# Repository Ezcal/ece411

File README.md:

# ece411
Practicum Project for ECE411 - Fall 2015
### Team Name: Sagutinhoun
### Group members:
Miguel Garcia de los Santos, Sabin Maharjan, Christina Nelson, and Calhoun Zabel

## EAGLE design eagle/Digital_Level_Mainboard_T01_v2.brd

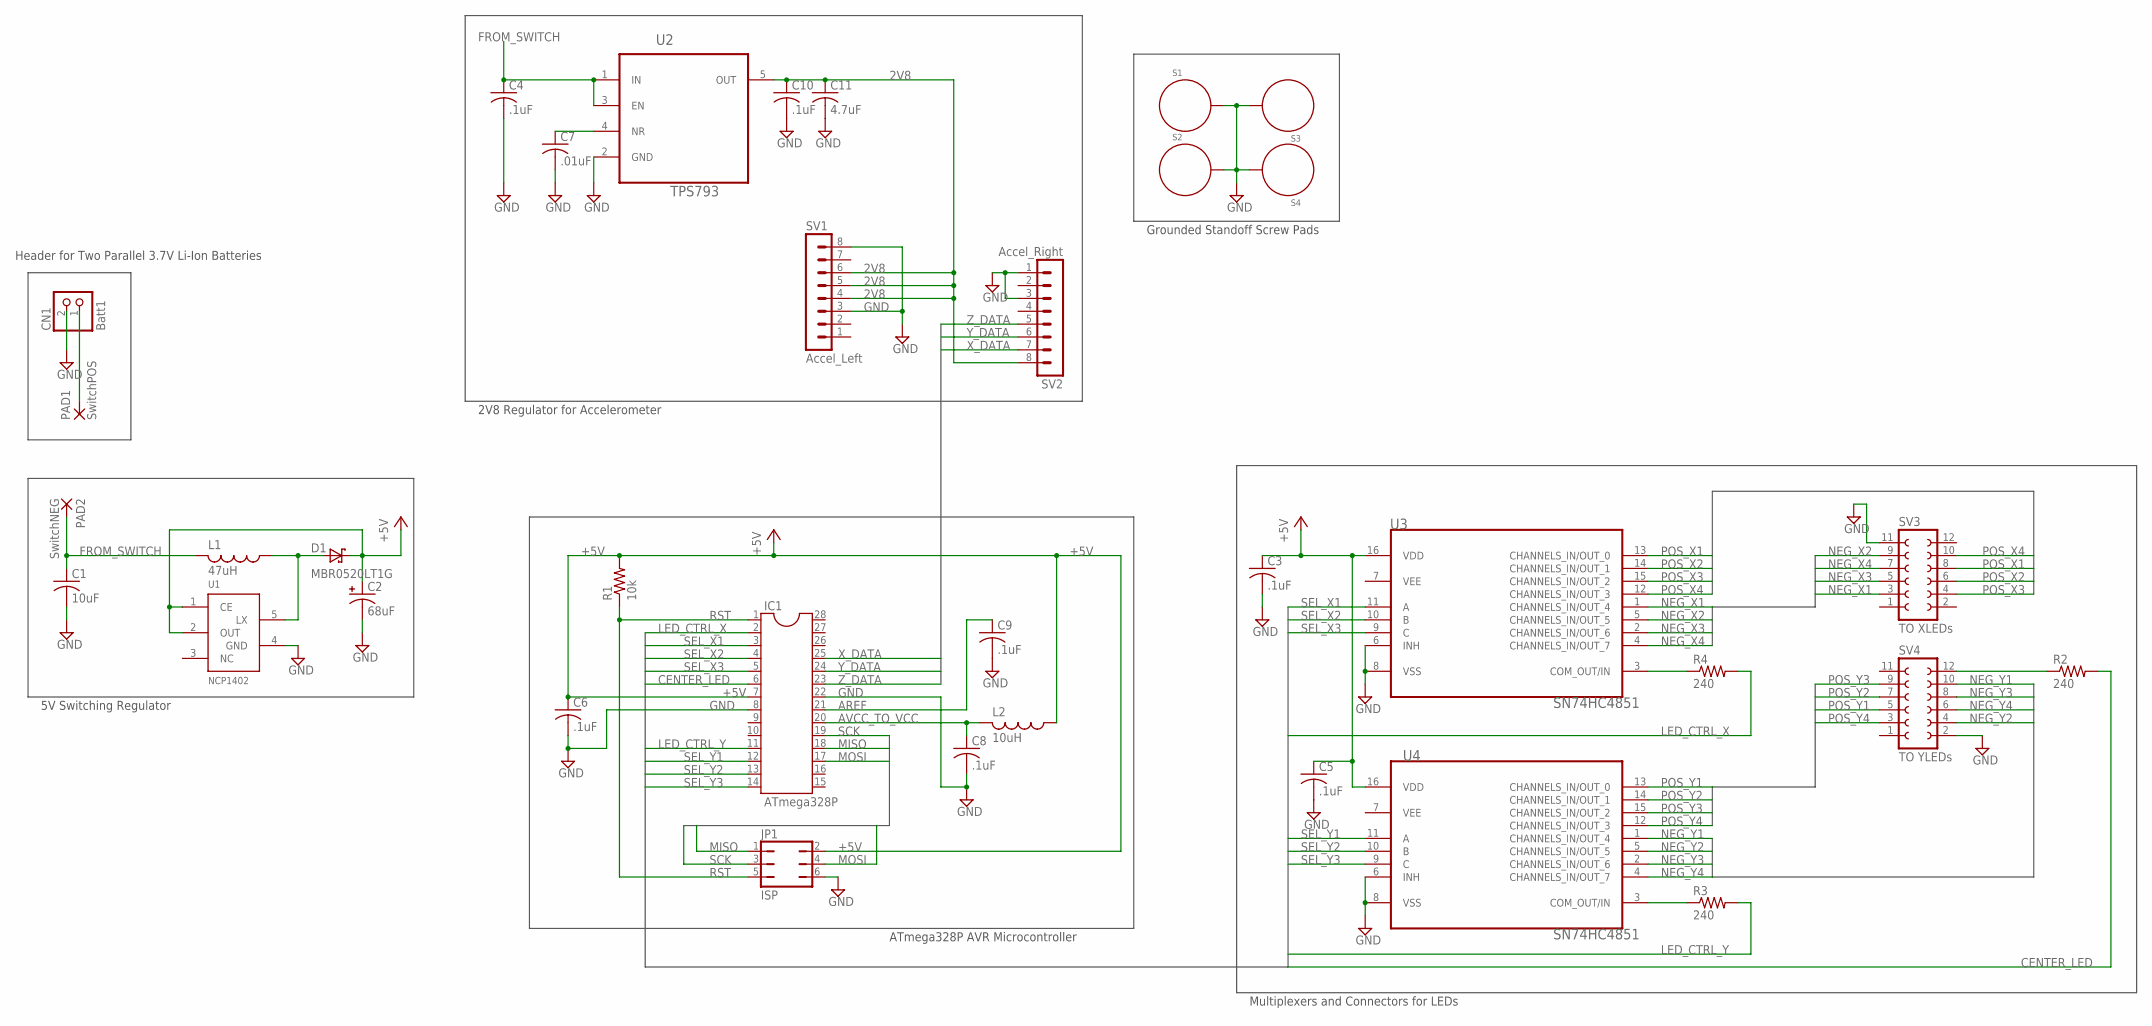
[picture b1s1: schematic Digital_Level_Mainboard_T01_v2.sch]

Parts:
C1: 10uF; C1206K
C2: 68uF; 2312_CAP
C3, C4, C5, C6, C8, C9, C10: .1uF; C1206K
C7: .01uF; C1206K
C11: 4.7uF; C1206K
CN1: Batt1; JST-PH-2-SMT
D1: MBR0520LT1G; MBR0520
IC1: ATmega328P; DIL28-3
JP1: ISP; JP3Q
L1: 47uH; BOURNS_INDUCTOR
L2: 10uH; L1812
PAD1: SwitchPOS; 2,54/1,1
PAD2: SwitchNEG; 2,54/1,1
R1: 10k; R0805
R2, R3, R4: 240; R1206
S1, S2, S3, S4: STANDOFF_ELECTRICAL; STANDOFF-ELECTRICAL
SV1: Accel_Left; MA08-1
SV2: Accel_Right; MA08-1
SV3: TO XLEDs; FE06-2
SV4: TO YLEDs; FE06-2
U1: NCP1402; WSON-8
U2: TPS793; SOT95P280X145-5N
U3, U4: SN74HC4851; DIP254P762X508-16

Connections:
2V8: C10.1, C11.1, SV1.4, SV1.5, SV1.6, SV2.8, U2.5 (OUT)
5V_REG1_LX: D1.P$2 (A), L1.P$1 (1), U1.5 (LX)
+5V: C2.P (1), C3.1, C5.1, C6.1, D1.P$1 (K), IC1.7, JP1.2, L2.1, R1.2, U1.1 (CE), U1.2 (OUT), U3.16 (VDD), U4.16 (VDD)
AREF: C9.1, IC1.21
AVCC_TO_VCC: C8.1, IC1.20, L2.2
CENTER_LED: IC1.6, R2.2
CENTER_LED_CONN: R2.1, SV4.12
CTRL_X_TO_MUX: R4.1, U3.3 (COM_OUT/IN)
CTRL_Y_TO_MUX: R3.1, U4.3 (COM_OUT/IN)
FROM_SWITCH: C1.1, C4.1, L1.P$2 (2), PAD2.1, U2.1 (IN), U2.3 (EN)
GND: C1.2, C2.N (2), C3.2, C4.2, C5.2, C6.2, C7.2, C8.2, C9.2, C10.2, C11.2, CN1.2 (1), IC1.8, IC1.22, JP1.6, S1.P1, S2.P1, S3.P1, S4.P1, SV1.3, SV1.8, SV2.1, SV2.3, SV3.11, SV4.2, U1.4 (GND), U2.2 (GND), U3.6 (INH), U3.8 (VSS), U4.6 (INH), U4.8 (VSS)
LED_CTRL_X: IC1.2, R4.2
LED_CTRL_Y: IC1.11, R3.2
LIN-REG_NR-PIN: C7.1, U2.4 (NR)
MISO: IC1.18, JP1.1
MOSI: IC1.17, JP1.4
NEG_X1: SV3.3, U3.1 (CHANNELS_IN/OUT_4)
NEG_X2: SV3.9, U3.5 (CHANNELS_IN/OUT_5)
NEG_X3: SV3.5, U3.2 (CHANNELS_IN/OUT_6)
NEG_X4: SV3.7, U3.4 (CHANNELS_IN/OUT_7)
NEG_Y1: SV4.10, U4.1 (CHANNELS_IN/OUT_4)
NEG_Y2: SV4.4, U4.5 (CHANNELS_IN/OUT_5)
NEG_Y3: SV4.8, U4.2 (CHANNELS_IN/OUT_6)
NEG_Y4: SV4.6, U4.4 (CHANNELS_IN/OUT_7)
POS_BATT: CN1.1 (2), PAD1.1
POS_X1: SV3.8, U3.13 (CHANNELS_IN/OUT_0)
POS_X2: SV3.6, U3.14 (CHANNELS_IN/OUT_1)
POS_X3: SV3.4, U3.15 (CHANNELS_IN/OUT_2)
POS_X4: SV3.10, U3.12 (CHANNELS_IN/OUT_3)
POS_Y1: SV4.5, U4.13 (CHANNELS_IN/OUT_0)
POS_Y2: SV4.7, U4.14 (CHANNELS_IN/OUT_1)
POS_Y3: SV4.9, U4.15 (CHANNELS_IN/OUT_2)
POS_Y4: SV4.3, U4.12 (CHANNELS_IN/OUT_3)
RST: IC1.1, JP1.5, R1.1
SCK: IC1.19, JP1.3
SEL_X1: IC1.3, U3.11 (A)
SEL_X2: IC1.4, U3.10 (B)
SEL_X3: IC1.5, U3.9 (C)
SEL_Y1: IC1.12, U4.11 (A)
SEL_Y2: IC1.13, U4.10 (B)
SEL_Y3: IC1.14, U4.9 (C)
X_DATA: IC1.25, SV2.7
Y_DATA: IC1.24, SV2.6
Z_DATA: IC1.23, SV2.5

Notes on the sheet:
Header for Two Parallel 3.7V Li-Ion Batteries
5V Switching Regulator
2V8 Regulator for Accelerometer
Grounded Standoff Screw Pads
Multiplexers and Connectors for LEDs
ATmega328P AVR Microcontroller

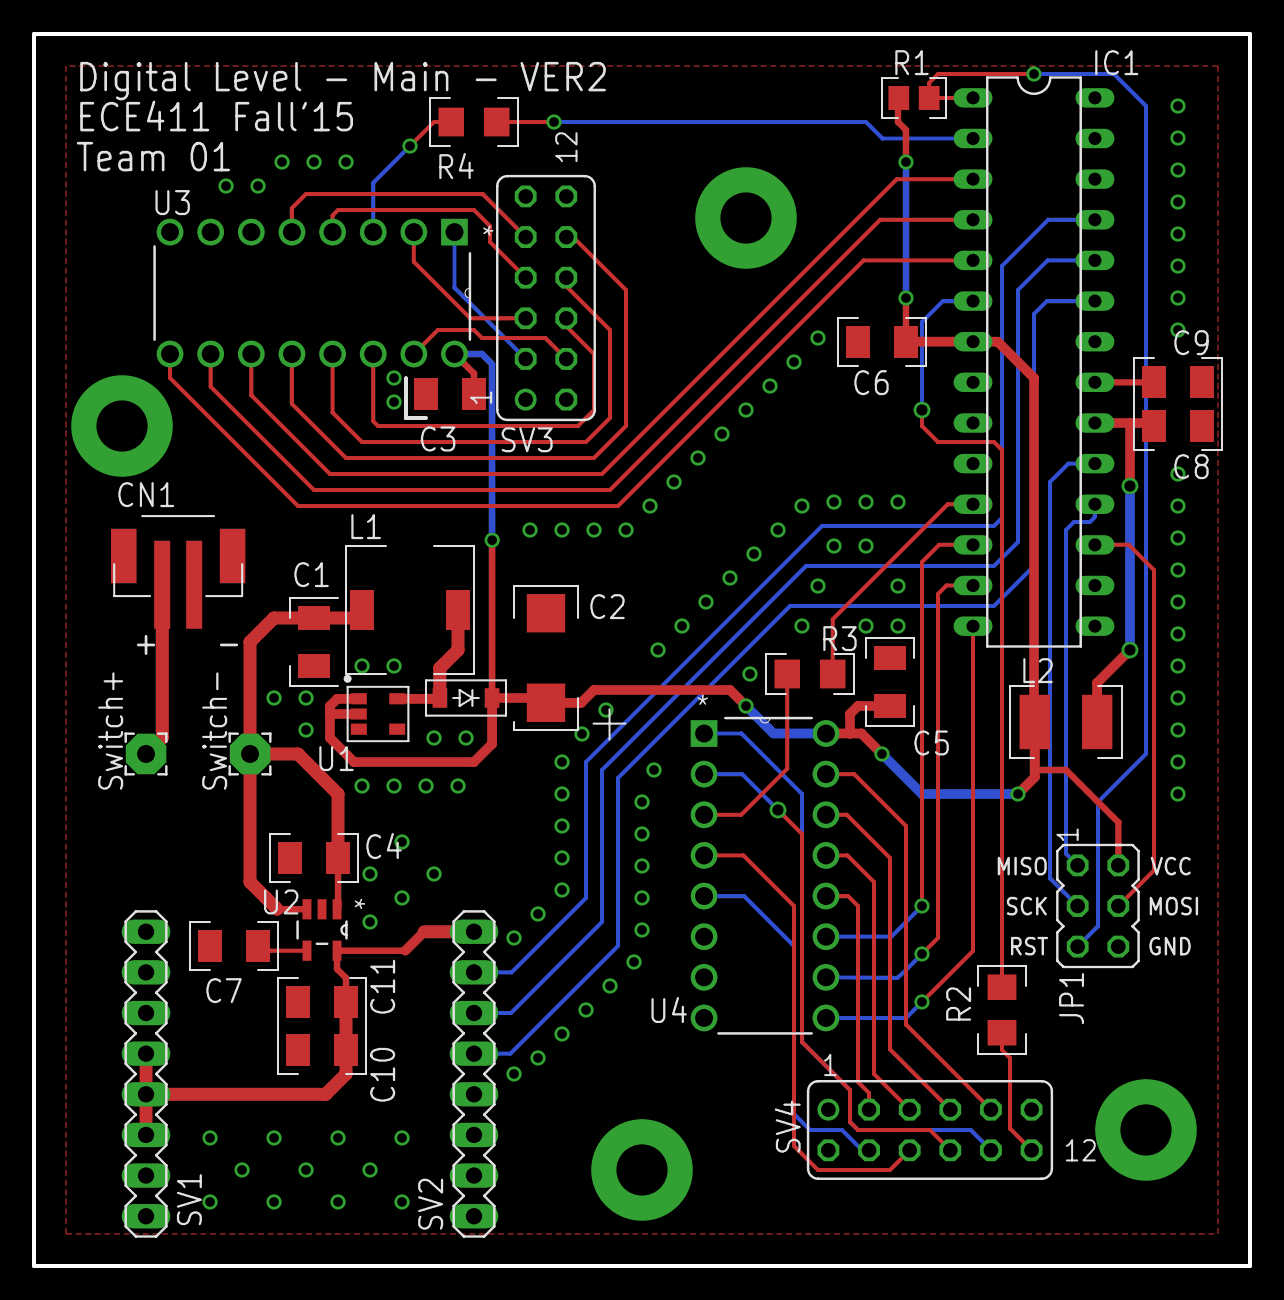
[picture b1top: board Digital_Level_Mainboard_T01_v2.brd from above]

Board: 2 copper layers, 76.0 x 77.0 mm, 35 parts (0 on the bottom side), 44 nets.

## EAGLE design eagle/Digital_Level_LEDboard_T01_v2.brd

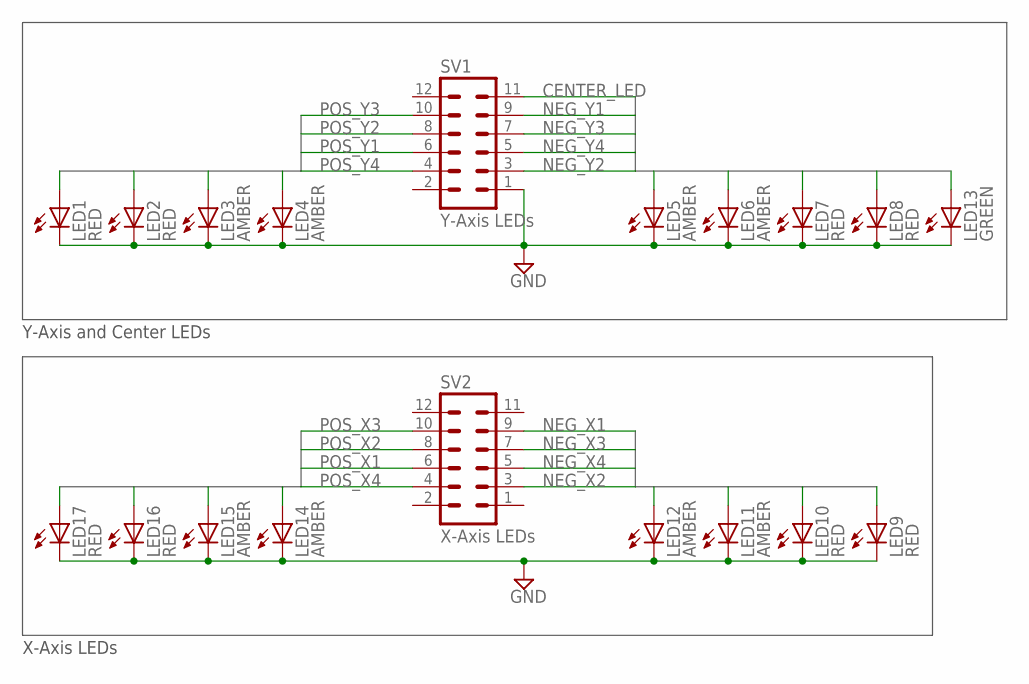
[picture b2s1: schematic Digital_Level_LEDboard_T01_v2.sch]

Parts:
LED1, LED2, LED7, LED8, LED9, LED10, LED16, LED17: RED; LED5MM
LED3, LED4, LED5, LED6, LED11, LED12, LED14, LED15: AMBER; LED5MM
LED13: GREEN; LED5MM
SV1: Y-Axis LEDs; MA06-2
SV2: X-Axis LEDs; MA06-2

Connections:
CENTER_LED: LED13.A, SV1.11
GND: LED1.K (C), LED2.K (C), LED3.K (C), LED4.K (C), LED5.K (C), LED6.K (C), LED7.K (C), LED8.K (C), LED9.K (C), LED10.K (C), LED11.K (C), LED12.K (C), LED13.K (C), LED14.K (C), LED15.K (C), LED16.K (C), LED17.K (C), SV1.1
NEG_X1: LED12.A, SV2.9
NEG_X2: LED11.A, SV2.3
NEG_X3: LED10.A, SV2.7
NEG_X4: LED9.A, SV2.5
NEG_Y1: LED5.A, SV1.9
NEG_Y2: LED6.A, SV1.3
NEG_Y3: LED7.A, SV1.7
NEG_Y4: LED8.A, SV1.5
POS_X1: LED14.A, SV2.6
POS_X2: LED15.A, SV2.8
POS_X3: LED16.A, SV2.10
POS_X4: LED17.A, SV2.4
POS_Y1: LED4.A, SV1.6
POS_Y2: LED3.A, SV1.8
POS_Y3: LED2.A, SV1.10
POS_Y4: LED1.A, SV1.4

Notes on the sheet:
Y-Axis and Center LEDs
X-Axis LEDs

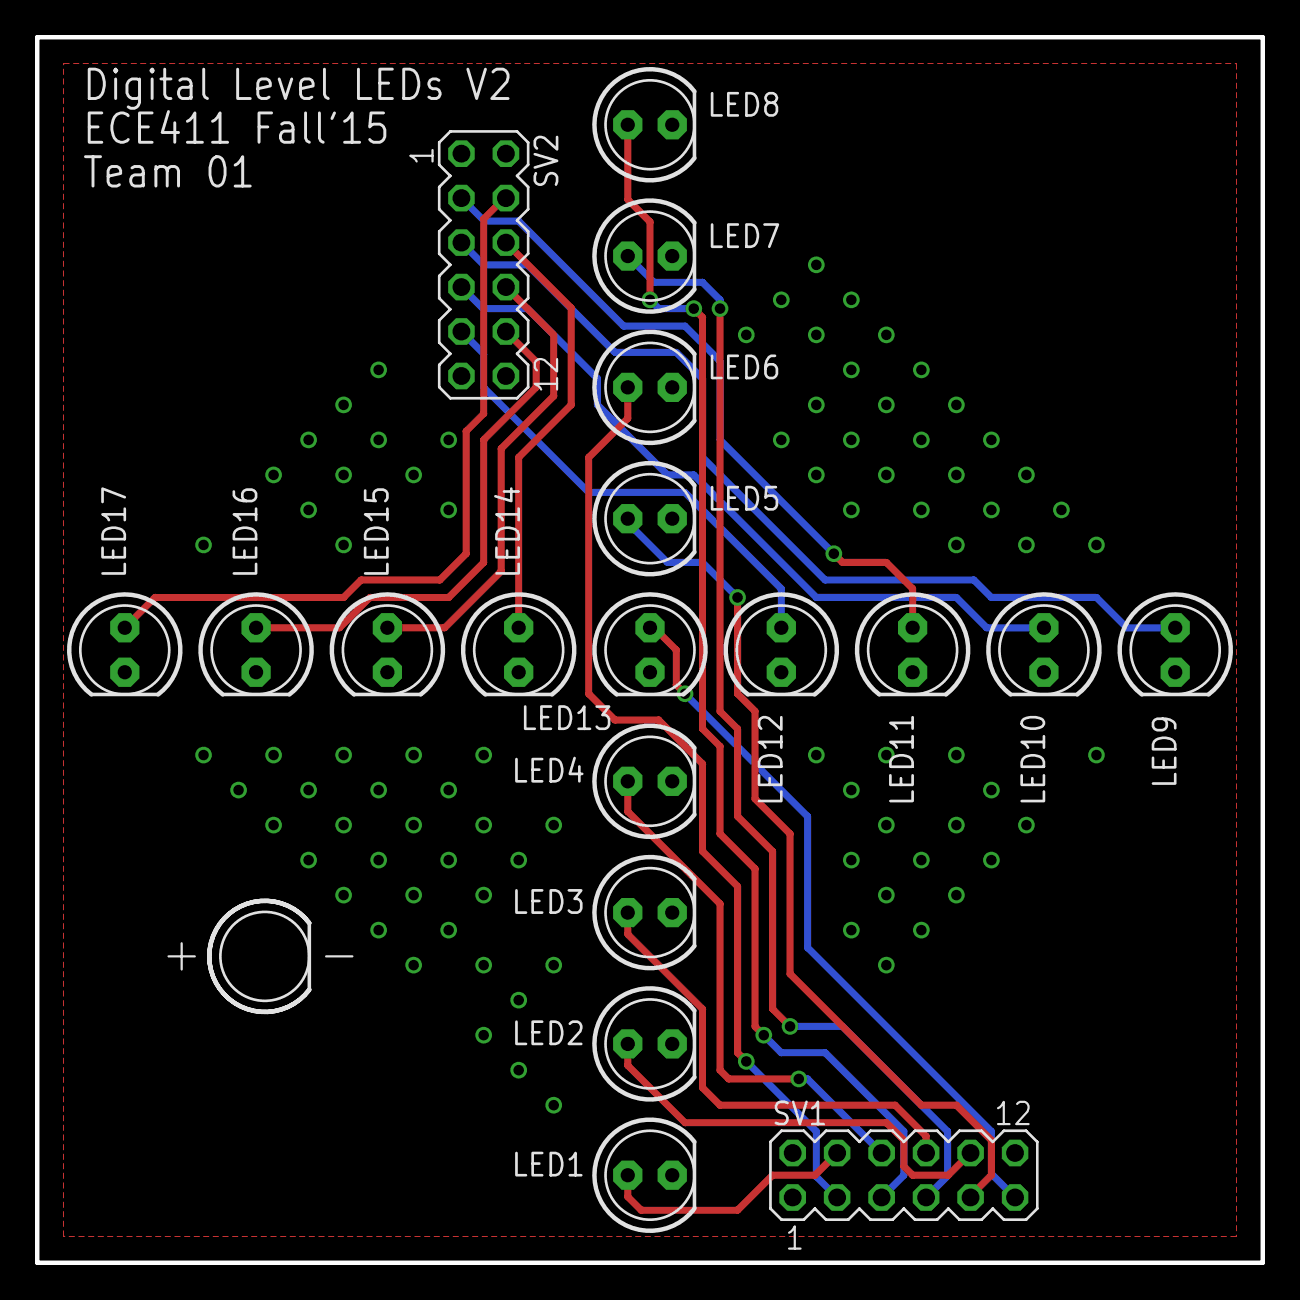
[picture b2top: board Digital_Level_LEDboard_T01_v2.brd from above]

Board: 2 copper layers, 70.0 x 70.0 mm, 19 parts (0 on the bottom side), 18 nets.

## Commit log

2015-10-02 Update README.md
    Changed Sabine to Sabin :)
2015-10-08 Create Project Ideas
2015-10-08 Update Project Ideas
2015-10-08 Create Parts Options
2015-10-09 Update Parts Options
2015-10-20 Schematic
    Current 10/19/2015
2015-10-21 Latest Schematic
2015-10-26 Create ADC
2015-10-27 Update ADC
2015-10-27 Create enums
2015-10-27 Update enums
2015-10-27 Create axis
2015-10-27 Update axis
2015-10-27 Create light_it_up_up_up
2015-10-27 Update light_it_up_up_up
2015-10-27 finally!
2015-10-28 Updated Schematic
2015-10-31 Update axis
    added range values
2015-11-02 fixed the port pins
2015-11-02 Create foo
2015-11-02 Create sdaf
2015-11-03 Update DigitalLevel.c
    changed ports
2015-11-05 gantt chart
2015-11-09 Update DigitalLevel.c
    Added Some comments on the functions
2015-11-10 Update DigitalLevel.c
    fixed some bug
2015-11-11 Code for Level by Cal
    Very basic, it might hurt your eyes
2015-11-13 Adding eagle files and directory
2015-11-15 New code by Cal
    New code using the internal 1.1V reference, and blocking center LED when
    either axis is off-centered
2015-12-07 Test Plan First Draft

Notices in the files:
parts and their libraries:
SparkFun-Electromechanical: Licensing: Creative Commons ShareAlike 4.0 International - https://creativecommons.org/licenses/by-sa/4.0
